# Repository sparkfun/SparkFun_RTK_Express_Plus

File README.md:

SparkFun RTK Express Plus
===========================================================

[*SparkFun RTK Express Plus (GPS-18590)*](https://www.sparkfun.com/products/18590)

he SparkFun RTK Express Plus is an easy to use GNSS receiver for centimeter-level positioning. Perfect for surveying, autonomous vehicles, logging, and all types of post processing, this preprogrammed device can also be used for autonomous driving, navigation, asset tracking and any other application where there is a clear view of the sky. The RTK Express Plus adds an internal IMU to combine real-time GNSS tracking with advanced sensor fusion. The result is accurate positioning even when GNSS is lost in tunnels, parking garages, etc. Out of the box an RTK Express Plus can be used with a correction source to create an RTK system capable of 14mm horizontal positional accuracy. The built-in Bluetooth® connection via an ESP32 WROOM enables the user to use the RTK Express Plus with their choice of GIS application on a phone or tablet. The built in battery allows for over five hours of field use and is compatible with common USB battery banks.

Repository Contents
-------------------

* **/Enclosure** - gcode for enclosure milling
* **/Graphics** - Bitmaps for the display
* **/Hardware** - Eagle files
* **/Overlay** - Design files for the adhesive membrane overlay

Documentation
--------------

* **[Hookup Guide](https://learn.sparkfun.com/tutorials/sparkfun-rtk-express-hookup-guide)** - Hookup guide for the SparkFun RTK Express.

License Information
-------------------

This product is _**open source**_!

Various bits of the code have different licenses applied. Anything SparkFun wrote is beerware; if you see me (or any other SparkFun employee) at the local, and you've found our code helpful, please buy us a round!

Please use, reuse, and modify these files as you see fit. Please maintain attribution to SparkFun Electronics and release anything derivative under the same license.

Distributed as-is; no warranty is given.

- Your friends at SparkFun.

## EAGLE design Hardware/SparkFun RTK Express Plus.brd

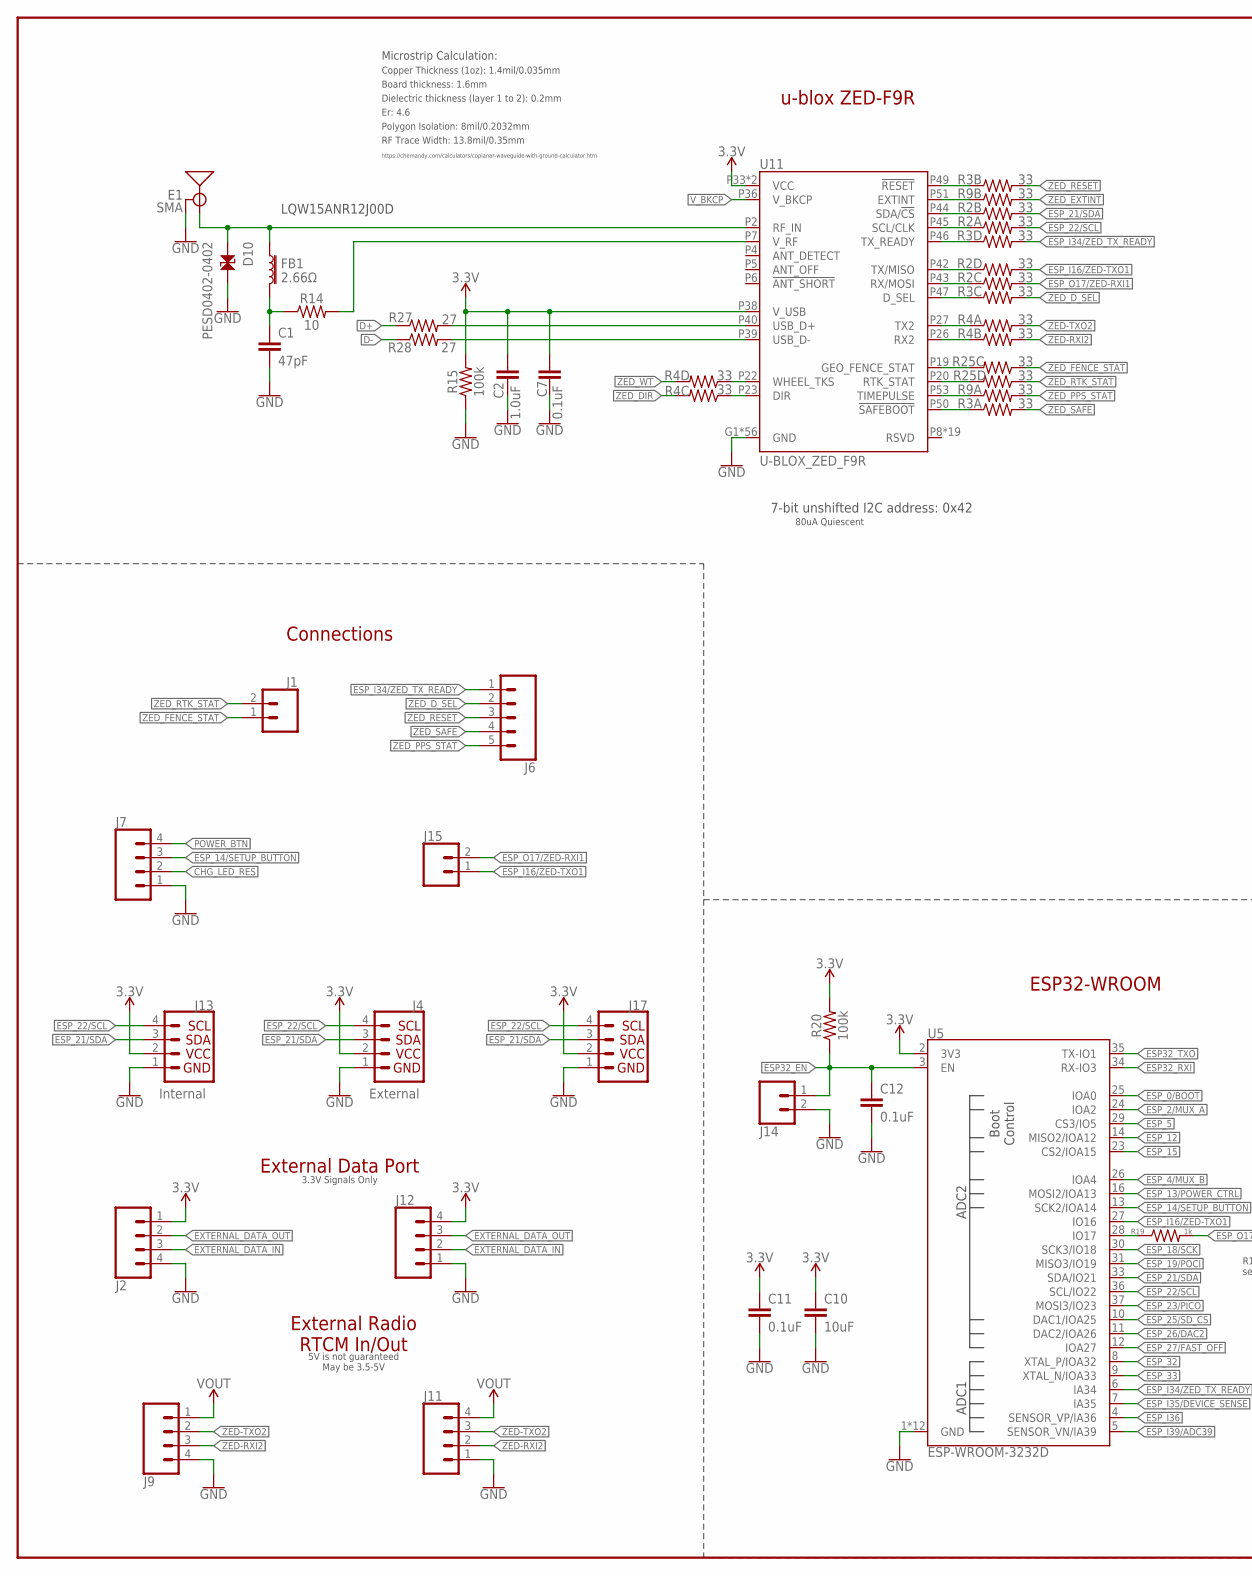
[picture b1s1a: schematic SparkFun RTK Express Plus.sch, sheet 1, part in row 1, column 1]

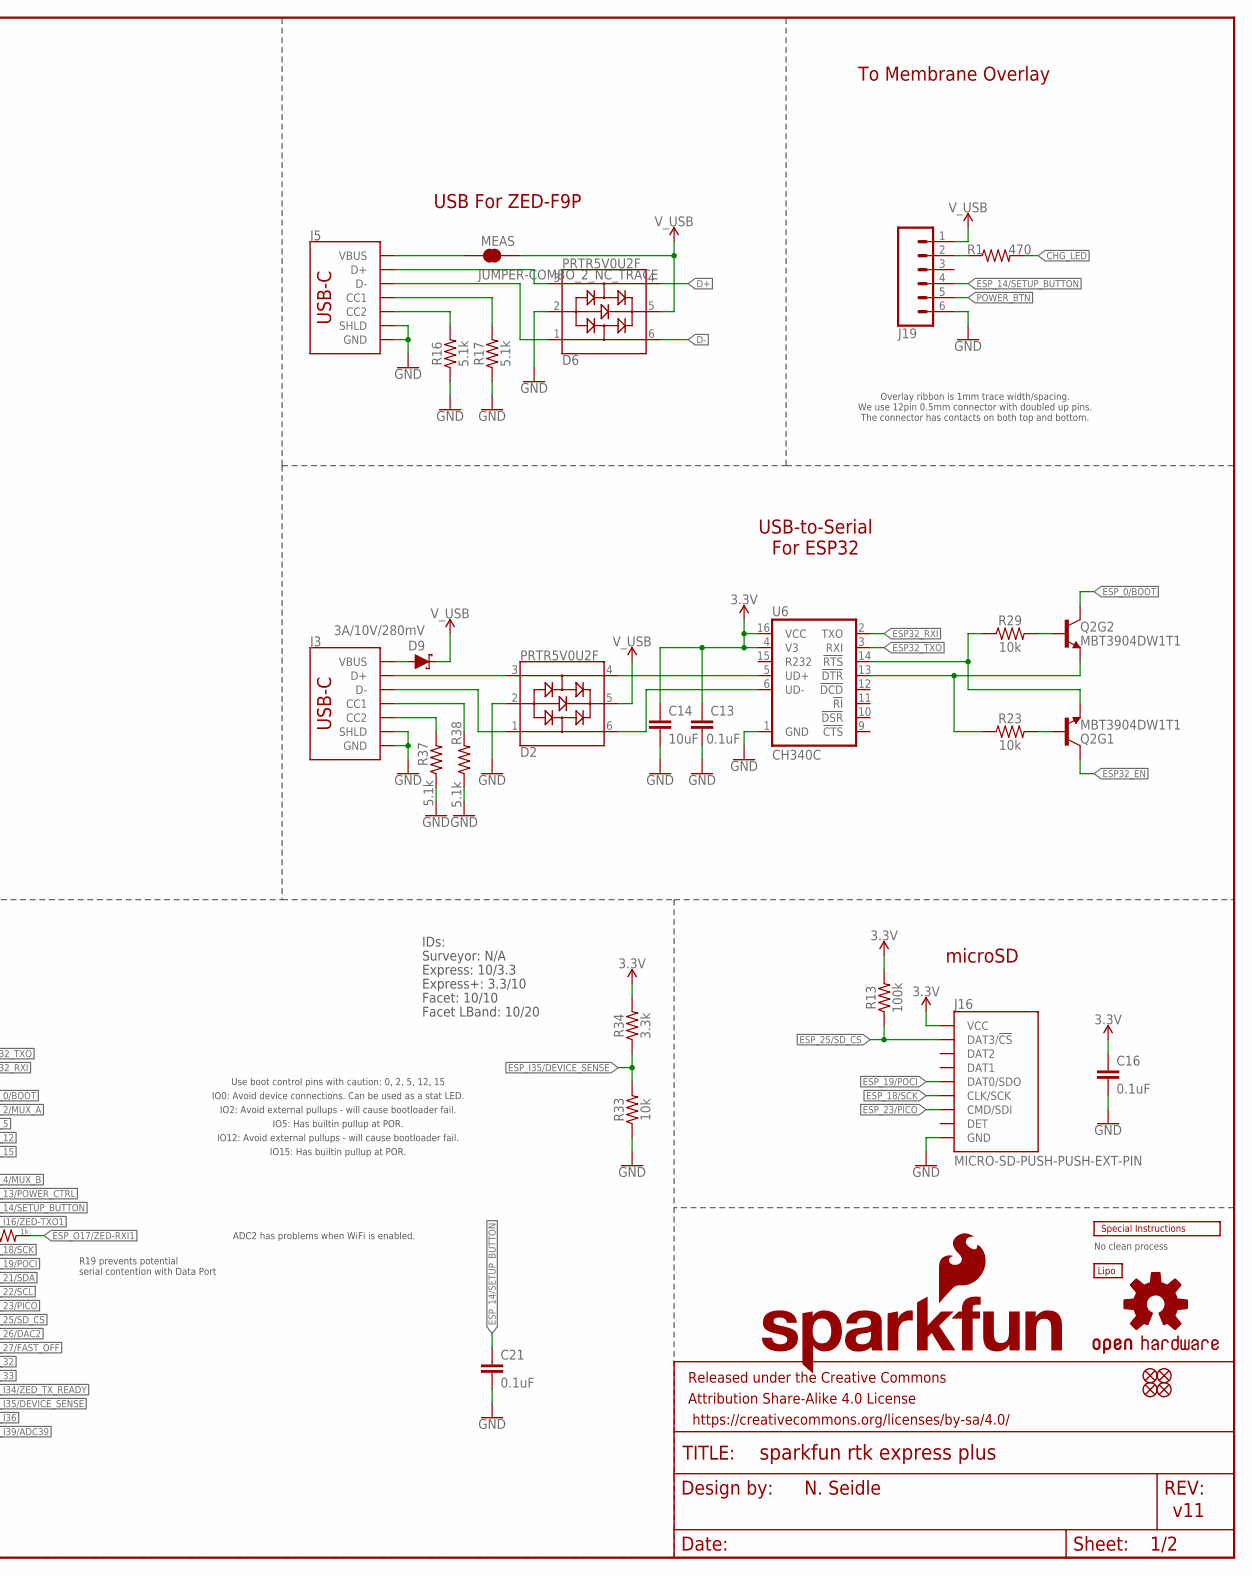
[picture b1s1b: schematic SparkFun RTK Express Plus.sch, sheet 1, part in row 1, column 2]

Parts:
BT1: LIPO-OUTLINE1000; LIPO-1000
C1: 47pF; 0402
C2: 1.0uF; 0603
C7, C11, C12, C13, C16, C21: 0.1uF; 0603
C10, C14: 10uF; 0603
D2, D6: PRTR5V0U2F; SOT886
D9: 3A/10V/280mV; SOD-323
D10: PESD0402-0402; 0402
E1: SMA; SMA-EDGE
FB1: 2.66Ω; 0402-TIGHT
FRAME2: FRAME-LEDGER; CREATIVE_COMMONS
J1, J14, J15: CONN_021X02_NO_SILK; 1X02_NO_SILK
J2, J9: CONN_04JST-SMD-LOCKING; JST-4-SMD-1.25MM-LOCKING
J3, J5: USB Female Type C Connector; USB-C-16P_4LAYER-PADS
J4: External; JST04_1MM_RA
J6: CONN_05NO_SILK; 1X05_NO_SILK
J7, J11, J12: CONN_041X04_NO_SILK_NO_POP; 1X04_NO_SILK
J13: Internal; JST04_1MM_RA
J16: MICRO-SD-PUSH-PUSH-EXT-PIN; MICROSD-EXTERNALPIN
J17: Qwiic Right Angle; 1X04_NO_SILK
J19: CONN_061MM-LIF; FPC_6_1MM-LIF
JP21, JP61, JP71, JP81: FIDUCIALUFIDUCIAL; FIDUCIAL-MICRO
LOGO1: OSHW-LOGOMINI; OSHW-LOGO-MINI
LOGO2: SFE_LOGO_NAME_FLAME.1_INCH; SFE_LOGO_NAME_FLAME_.1
MEAS: JUMPER-COMBO_2_NC_TRACE; COMBO-JUMPER_2_NC_TRACE
Q2: MBT3904DW1T1; SC70-6
R1: 470; 0603
R2, R3, R4, R9, R25: 33; 1206_RA
R13, R15, R20: 100k; 0603
R14: 10; 0603
R16, R17, R37, R38: 5.1k; 0603
R19: 1k; 0603
R23, R29, R33: 10k; 0603
R27, R28: 27; 0603
R34: 3.3k; 0603
U5: ESP-WROOM-3232D; ESP-WROOM-32D
U6: CH340C; SO016
U11: U-BLOX_ZED_F9R; UBLOX_ZED_F9R
U$2: SPECIAL_INSTRUCTIONS-ORDERING; ORDERING_INSTRUCTIONS

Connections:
3.3V: C2.1, C7.2, C10.1, C11.1, C13.1, C14.1, C16.1, J2.1, J4.2, J12.4, J13.2, J16.4 (VCC), J17.2, R13.2, R15.2, R20.2, R34.2, U5.2 (3V3), U6.4 (V3), U6.16 (VCC), U11.P33 (VCC), U11.P34 (VCC), U11.P38 (V_USB); also elsewhere on the board
ANT_VCC: C1.1, FB1.2, R14.1
CC1: J5.A5 (CC1), R17.2
CC2: J5.B5 (CC2), R16.2
CC3: J3.B5 (CC2), R37.2
CC4: J3.A5 (CC1), R38.2
CHG_LED: R1.2; also elsewhere on the board
CHG_LED_RES: J7.2, J19.2, R1.1
D+: D6.4, R27.1
D+1: D2.4, U6.5 (UD+)
D-: D6.6, R28.1
D-1: D2.6, U6.6 (UD-)
ESP32_!DTR: Q2.1 (E), R23.1, U6.13 (!DTR)
ESP32_!RTS: Q2.4 (E), R29.1, U6.14 (!RTS)
ESP32_EN: C12.1, J14.1, Q2.3 (C), R20.1, U5.3 (EN)
ESP32_RXI: U5.34 (RX-IO3), U6.2 (TXO)
ESP32_TXO: U5.35 (TX-IO1), U6.3 (RXI)
ESP_0/BOOT: Q2.6 (C), U5.25 (IOA0)
ESP_2/MUX_A: U5.24 (IOA2); also elsewhere on the board
ESP_4/MUX_B: U5.26 (IOA4); also elsewhere on the board
ESP_5: U5.29 (CS3/IO5)
ESP_12: U5.14 (MISO2/IOA12)
ESP_13/POWER_CTRL: U5.16 (MOSI2/IOA13); also elsewhere on the board
ESP_14/SETUP_BUTTON: C21.1, J7.3, J19.4, U5.13 (SCK2/IOA14)
ESP_15: U5.23 (CS2/IOA15)
ESP_18/SCK: J16.5 (CLK/SCK), U5.30 (SCK3/IO18)
ESP_19/POCI: J16.7 (DAT0/SDO), U5.31 (MISO3/IO19)
ESP_21/SDA: J4.3, J13.3, J17.3, R2.P7 (2), U5.33 (SDA/IO21); also elsewhere on the board
ESP_22/SCL: J4.4, J13.4, J17.4, R2.P8 (2), U5.36 (SCL/IO22); also elsewhere on the board
ESP_23/PICO: J16.3 (CMD/SDI), U5.37 (MOSI3/IO23)
ESP_25/SD_!CS!: J16.2 (DAT3/!CS!), R13.1, U5.10 (DAC1/IOA25)
ESP_26/DAC2: U5.11 (DAC2/IOA26); also elsewhere on the board
ESP_26/ZED_TX_READY_LV: R3.P4 (1), U11.P46 (TX_READY)
ESP_27/FAST_OFF: U5.12 (IOA27); also elsewhere on the board
ESP_32: U5.8 (XTAL_P/IOA32)
ESP_33: U5.9 (XTAL_N/IOA33)
ESP_D1+: D2.3, J3.A6 (D+), J3.B6 (D+)
ESP_D1-: D2.1, J3.A7 (D-), J3.B7 (D-)
ESP_I16/ZED-TXO1: J15.1, R2.P5 (2), U5.27 (IO16); also elsewhere on the board
ESP_I34/ZED_TX_READY: J6.1, R3.P5 (2), U5.6 (IA34)
ESP_I35/DEVICE_SENSE: R33.2, R34.1, U5.7 (IA35)
ESP_I36: U5.4 (SENSOR_VP/IA36)
ESP_I39/ADC39: U5.5 (SENSOR_VN/IA39); also elsewhere on the board
ESP_O17/ZED-RXI1: J15.2, R2.P6 (2), R19.2; also elsewhere on the board
EXTERNAL_DATA_IN: J2.3, J12.2; also elsewhere on the board
EXTERNAL_DATA_OUT: J2.2, J12.3; also elsewhere on the board
EXTINT_LV: R9.P2 (1), U11.P51 (EXTINT)
FENCE_LV: R25.P6 (2), U11.P19 (GEO_FENCE_STAT)
GND: C1.2, C2.2, C7.1, C10.2, C11.2, C12.2, C13.2, C14.2, C16.2, C21.2, D2.2, D6.2, D10.2, E1.GND@0 (GND), E1.GND@1 (GND), E1.GND@2 (GND), E1.GND@3 (GND), J2.4, J3.GND, J3.GND2 (GND), J3.SHLD1 (SHLD), J3.SHLD2 (SHLD), J3.SHLD3 (SHLD), J3.SHLD4 (SHLD), J4.1, J5.GND, J5.GND2 (GND), J5.SHLD1 (SHLD), J5.SHLD2 (SHLD), J5.SHLD3 (SHLD), J5.SHLD4 (SHLD), J7.1, J9.4, J11.1, J12.1, J13.1, J14.2, J16.6 (GND), J16.10 (GND), J16.11 (GND), J16.12 (GND), J16.13 (GND), J17.1, J19.6, R15.1, R16.1, R17.1, R33.1, R37.1, R38.1, U5.1 (GND), U5.15 (GND), U5.38 (GND), U5.GND, U5.GNDT1 (GND), U5.GNDT2 (GND), U5.GNDT3 (GND), U5.GNDT4 (GND), U5.GNDT5 (GND), U5.GNDT6 (GND), U5.GNDT7 (GND), U5.GNDT8 (GND), U6.1 (GND), U11.G1 (GND), U11.G2 (GND), U11.G3 (GND), U11.G4 (GND), U11.G5 (GND), U11.G6 (GND), U11.G7 (GND), U11.G8 (GND), U11.G9 (GND), U11.G10 (GND), U11.G11 (GND), U11.G12 (GND), U11.G13 (GND), U11.G14 (GND), U11.G15 (GND), U11.G16 (GND), U11.G17 (GND), U11.G18 (GND), U11.G19 (GND), U11.G20 (GND), U11.G21 (GND), U11.G22 (GND), U11.G23 (GND), U11.G24 (GND), U11.G25 (GND), U11.G26 (GND), U11.G27 (GND), U11.G28 (GND), U11.G29 (GND), U11.G30 (GND), U11.G31 (GND), U11.G32 (GND), U11.G33 (GND), U11.G34 (GND), U11.G35 (GND), U11.G36 (GND), U11.G37 (GND), U11.G38 (GND), U11.G39 (GND), U11.G40 (GND), U11.G41 (GND), U11.G42 (GND), U11.G43 (GND), U11.G44 (GND), U11.G45 (GND), U11.G46 (GND), U11.G47 (GND), U11.G48 (GND), U11.P1 (GND), U11.P3 (GND), U11.P12 (GND), U11.P14 (GND), U11.P32 (GND), U11.P37 (GND), U11.P41 (GND), U11.P48 (GND); also elsewhere on the board
GPS_ANT1: D10.1, E1.SIG (SIGNAL), FB1.1, U11.P2 (RF_IN)
unnamed: R4.P4 (1), U11.P22 (WHEEL_TKS)
unnamed: R4.P3 (1), U11.P23 (DIR)
unnamed: J5.VBUS1 (VBUS), J5.VBUS2 (VBUS), MEAS.1, MEAS.3 (1)
unnamed: R19.1, U5.28 (IO17)
unnamed: R27.2, U11.P40 (USB_D+)
unnamed: R28.2, U11.P39 (USB_D-)
unnamed: R14.2, U11.P7 (V_RF)
unnamed: Q2.5 (B), R23.2
unnamed: Q2.2 (B), R29.2
unnamed: D9.A, J3.VBUS1 (VBUS), J3.VBUS2 (VBUS)
POWER_BTN: J7.4, J19.5; also elsewhere on the board
PPS_LV: R9.P1 (1), U11.P53 (TIMEPULSE)
RTK_STAT_LV: R25.P5 (2), U11.P20 (RTK_STAT)
RX2_LV: R4.P2 (1), U11.P26 (RX2)
RXLV: R2.P3 (1), U11.P43 (RX/MOSI)
SCL_LV: R2.P1 (1), U11.P45 (SCL/CLK)
SDA_LV: R2.P2 (1), U11.P44 (SDA/!CS!)
TX2_LV: R4.P1 (1), U11.P27 (TX2)
TXLV: R2.P4 (1), U11.P42 (TX/MISO)
UNP_D+: D6.3, J5.A6 (D+), J5.B6 (D+)
UNP_D-: D6.1, J5.A7 (D-), J5.B7 (D-)
VOUT: J9.1, J11.4; also elsewhere on the board
V_BKCP: U11.P36 (V_BKCP); also elsewhere on the board
V_USB: D2.5, D6.5, D9.C, J19.1, MEAS.2, MEAS.4 (2); also elsewhere on the board
ZED-RXI2: J9.3, J11.2, R4.P7 (2)
ZED-TXO2: J9.2, J11.3, R4.P8 (2)
ZED_!RESET!: J6.3, R3.P7 (2)
ZED_!RESET!_LV: R3.P2 (1), U11.P49 (!RESET!)
ZED_!SAFE!: J6.4, R3.P8 (2)
ZED_!SAFE!_LV: R3.P1 (1), U11.P50 (!SAFEBOOT!)
ZED_DIR: R4.P6 (2); also elsewhere on the board
ZED_D_SEL: J6.2, R3.P6 (2)
ZED_D_SEL_LV: R3.P3 (1), U11.P47 (D_SEL)
ZED_EXTINT: R9.P7 (2); also elsewhere on the board
ZED_FENCE_STAT: J1.1, R25.P3 (1)
ZED_PPS_STAT: J6.5, R9.P8 (2); also elsewhere on the board
ZED_RTK_STAT: J1.2, R25.P4 (1)
ZED_WT: R4.P5 (2); also elsewhere on the board

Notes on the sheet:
v11
7-bit unshifted I2C address: 0x42
u-blox ZED-F9R
LQW15ANR12J00D
Board thickness: 1.6mm
Er: 4.6
Copper Thickness (1oz): 1.4mil/0.035mm
RF Trace Width: 13.8mil/0.35mm
Polygon Isolation: 8mil/0.2032mm
No clean process
Dielectric thickness (layer 1 to 2): 0.2mm
https://chemandy.com/calculators/coplanar-waveguide-with-ground-calculator.htm
Microstrip Calculation:
Connections
External Radio RTCM In/Out
External Data Port
ESP32-WROOM
USB-to-Serial For ESP32
microSD
5V is not guaranteed May be 3.5-5V
USB For ZED-F9P
N. Seidle
R19 prevents potential serial contention with Data Port
80uA Quiescent
To Membrane Overlay
Overlay ribbon is 1mm trace width/spacing. We use 12pin 0.5mm connector with doubled up pins. The connector has contacts on both top and bottom.
IO0: Avoid device connections. Can be used as a stat LED.
ADC2 has problems when WiFi is enabled.
IO12: Avoid external pullups - will cause bootloader fail.
Use boot control pins with caution: 0, 2, 5, 12, 15
IO2: Avoid external pullups - will cause bootloader fail.
IO15: Has builtin pullup at POR.
IO5: Has builtin pullup at POR.
3.3V Signals Only
IDs:
Surveyor: N/A
Express: 10/3.3
Express+: 3.3/10
Facet: 10/10
Facet LBand: 10/20

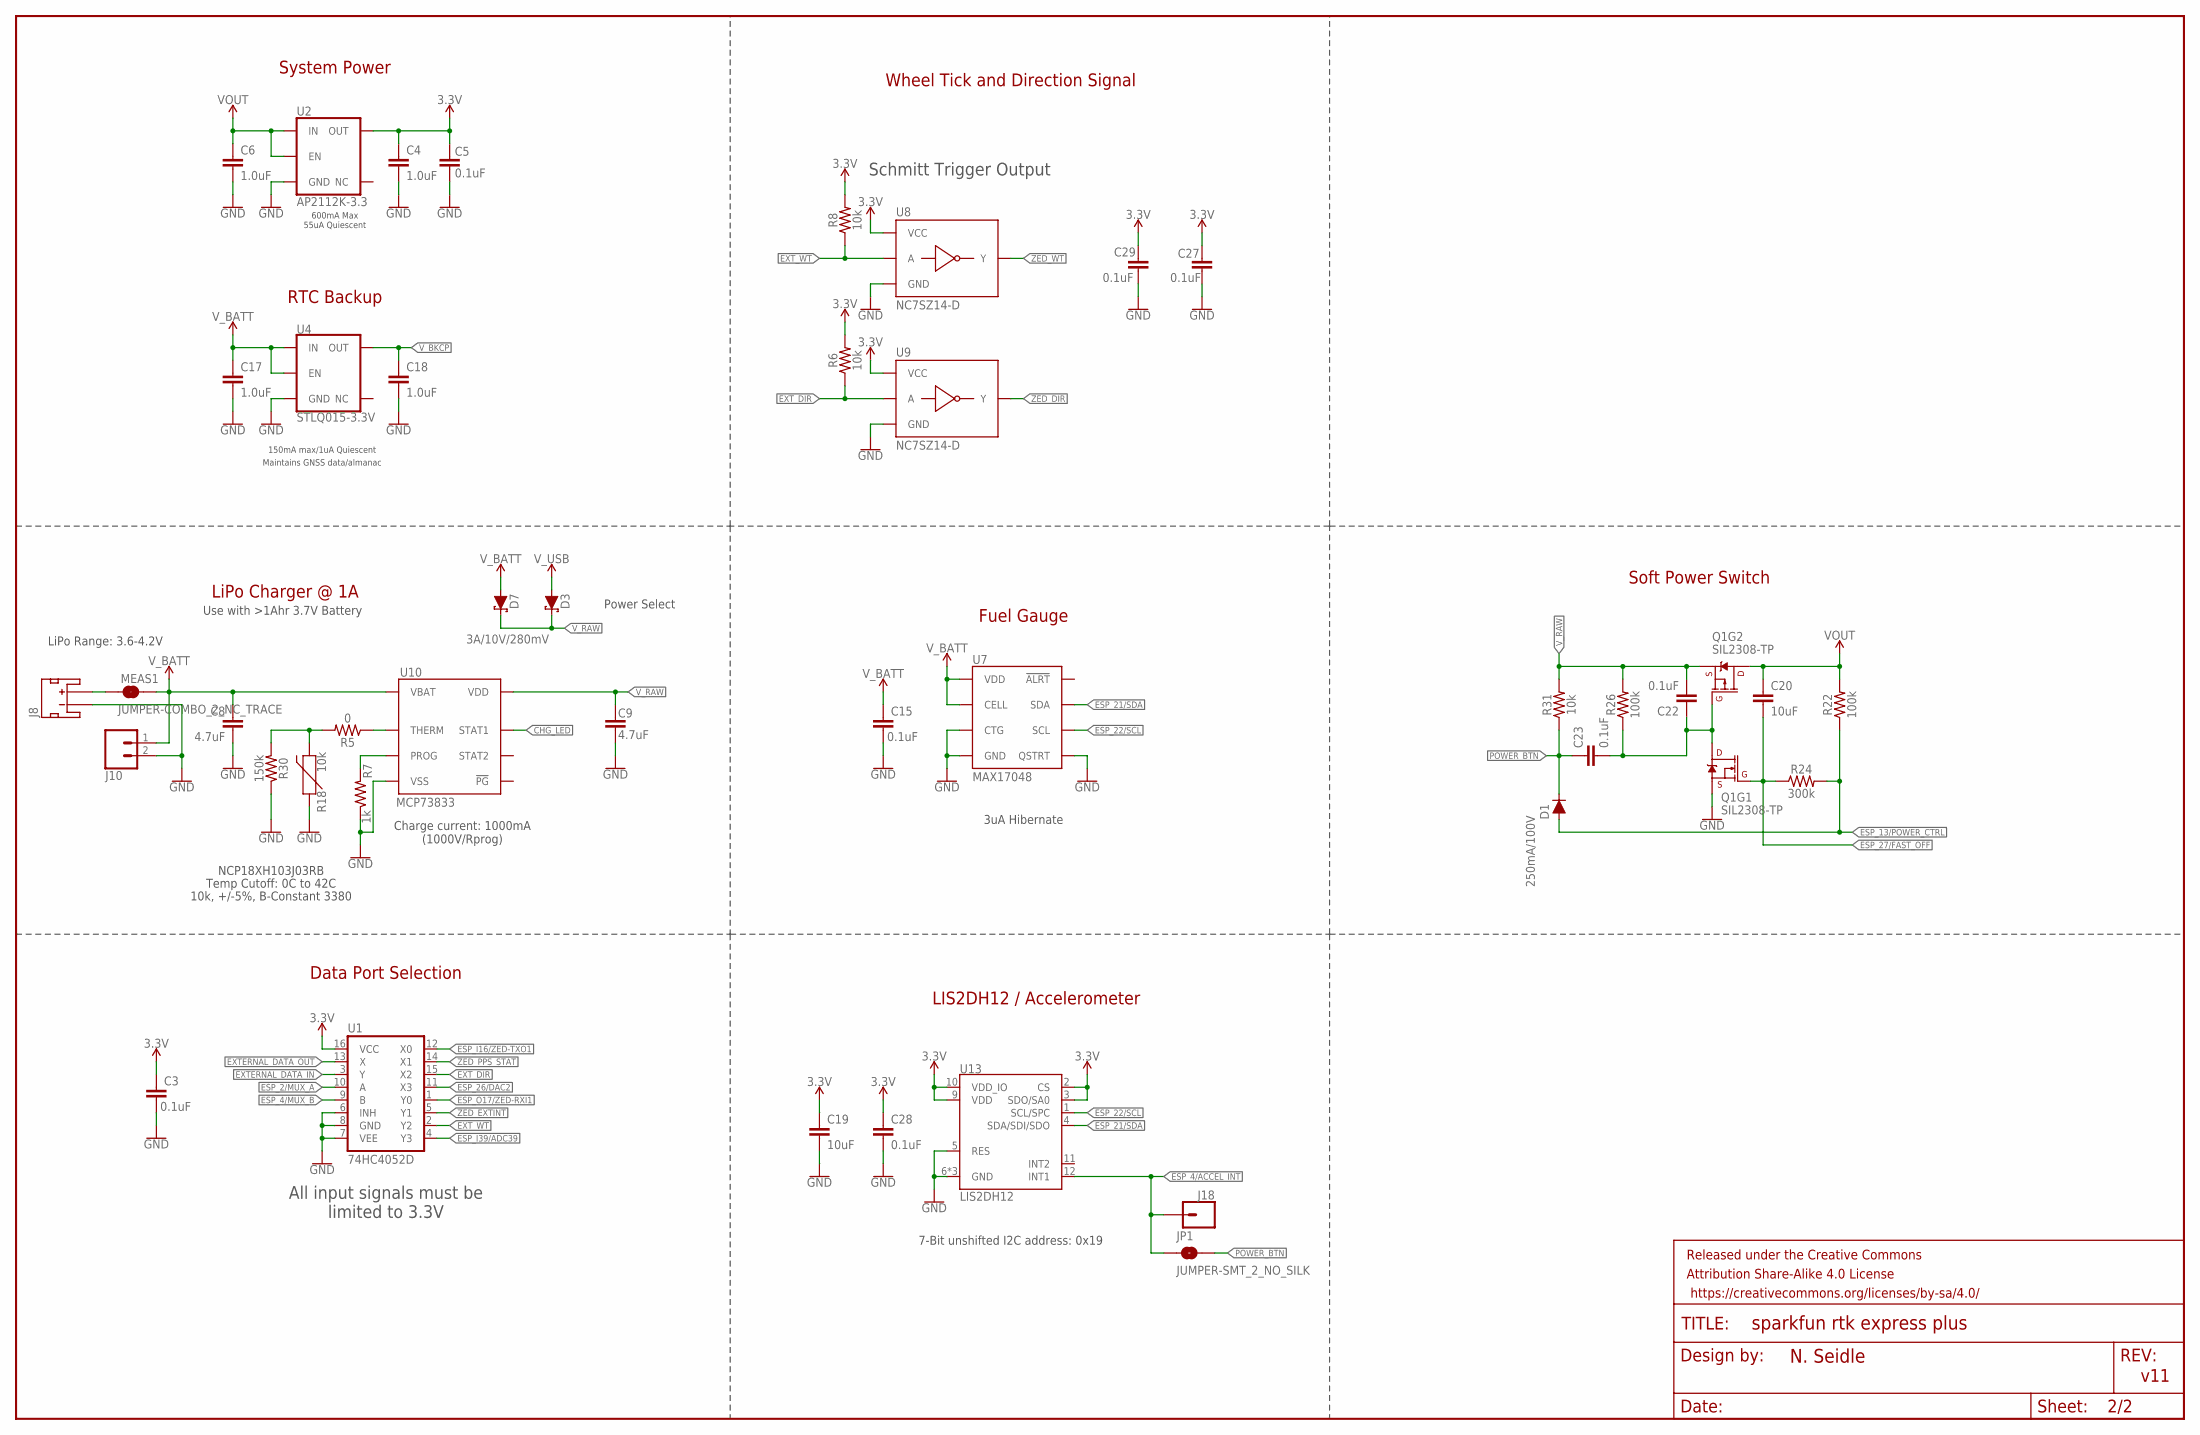
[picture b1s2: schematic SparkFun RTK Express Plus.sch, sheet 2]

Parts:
C3, C5, C15, C22, C23, C27, C28, C29: 0.1uF; 0603
C4, C6, C17, C18: 1.0uF; 0603
C8, C9: 4.7uF; 0603
C19, C20: 10uF; 0603
D1: 250mA/100V; SOD-323
D3, D7: 3A/10V/280mV; SOD-323
FRAME3: FRAME-LEDGERNO_FOOTPRINT; DUMMY
J8: JST_2MM_MALE; JST-2-SMD
J10: CONN_021X02_NO_SILK; 1X02_NO_SILK
J18: CONN_01PTH_NO_SILK_YES_STOP; 1X01_NO_SILK
JP1: JUMPER-SMT_2_NO_SILK; SMT-JUMPER_2_NO_SILK
MEAS1: JUMPER-COMBO_2_NC_TRACE; COMBO-JUMPER_2_NC_TRACE
Q1: SIL2308-TP; SOT26
R5: 0; 0603
R6, R8, R18, R31: 10k; 0603
R7: 1k; 0603
R22, R26: 100k; 0603
R24: 300k; 0603
R30: 150k; 0603
U1: 74HC4052D; SO16
U2: AP2112K-3.3; SOT23-5
U4: STLQ015-3.3V; SOT23-5
U7: MAX17048; DFN-8
U8, U9: NC7SZ14-D; SIP6
U10: MCP73833; DFN-10
U13: LIS2DH12; LGA-12-LISDH12

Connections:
3.3V: C3.1, C4.1, C5.2, C19.1, C27.1, C28.1, C29.1, R6.2, R8.2, U1.16 (VCC), U2.5 (OUT), U8.P6 (VCC), U9.P6 (VCC), U13.2 (CS), U13.3 (SDO/SA0), U13.9 (VDD), U13.10 (VDD_IO); also elsewhere on the board
CHG_LED: U10.3 (STAT1); also elsewhere on the board
CHG_THERM1: R5.2, R18.2, R30.2
ESP_2/MUX_A: U1.10 (A); also elsewhere on the board
ESP_4/ACCEL_INT: J18.1, JP1.1, U13.12 (INT1)
ESP_4/MUX_B: U1.9 (B); also elsewhere on the board
ESP_13/POWER_CTRL: D1.A, R22.1, R24.2; also elsewhere on the board
ESP_21/SDA: U7.8 (SDA), U13.4 (SDA/SDI/SDO); also elsewhere on the board
ESP_22/SCL: U7.7 (SCL), U13.1 (SCL/SPC); also elsewhere on the board
ESP_26/DAC2: U1.11 (X3); also elsewhere on the board
ESP_27/FAST_OFF: C20.2, Q1.G1 (G), R24.1; also elsewhere on the board
ESP_I16/ZED-TXO1: U1.12 (X0); also elsewhere on the board
ESP_I39/ADC39: U1.4 (Y3); also elsewhere on the board
ESP_O17/ZED-RXI1: U1.1 (Y0); also elsewhere on the board
EXTERNAL_DATA_IN: U1.3 (Y); also elsewhere on the board
EXTERNAL_DATA_OUT: U1.13 (X); also elsewhere on the board
EXT_DIR: R6.1, U1.15 (X2), U9.P2 (A)
EXT_WT: R8.1, U1.2 (Y2), U8.P2 (A)
GND: C3.2, C4.2, C5.1, C6.2, C8.2, C9.2, C15.2, C17.2, C18.2, C19.2, C27.2, C28.2, C29.2, J8.1 (-), J10.2, Q1.S1 (S), R7.1, R18.1, R30.1, U1.6 (INH), U1.7 (VEE), U1.8 (GND), U2.2 (GND), U4.2 (GND), U7.1 (CTG), U7.4 (GND), U7.6 (QSTRT), U7.9 (GND), U8.P3 (GND), U9.P3 (GND), U10.5 (VSS), U10.11 (VSS), U13.5 (RES), U13.6 (GND), U13.7 (GND), U13.8 (GND); also elsewhere on the board
LIPO_RAW: J8.2 (+), MEAS1.1, MEAS1.3 (1)
unnamed: R5.1, U10.8 (THERM)
unnamed: C22.1, C23.2, Q1.D1 (D), Q1.G2 (G), R26.1
POWER_BTN: C23.1, D1.C, JP1.2, R31.1; also elsewhere on the board
PROG1: R7.2, U10.6 (PROG)
VOUT: C6.1, C20.1, Q1.D2 (D), R22.2, U2.1 (IN), U2.3 (EN); also elsewhere on the board
V_BATT: C8.1, C15.1, C17.1, D7.A, J10.1, MEAS1.2, MEAS1.4 (2), U4.1 (IN), U4.3 (EN), U7.2 (CELL), U7.3 (VDD), U10.9 (VBAT), U10.10 (VBAT)
V_BKCP: C18.1, U4.5 (OUT); also elsewhere on the board
V_RAW: C9.1, C22.2, D3.C, D7.C, Q1.S2 (S), R26.2, R31.2, U10.1 (VDD), U10.2 (VDD)
V_USB: D3.A; also elsewhere on the board
ZED_DIR: U9.P4 (Y); also elsewhere on the board
ZED_EXTINT: U1.5 (Y1); also elsewhere on the board
ZED_PPS_STAT: U1.14 (X1); also elsewhere on the board
ZED_WT: U8.P4 (Y); also elsewhere on the board

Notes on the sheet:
LiPo Range: 3.6-4.2V
Charge current: 1000mA (1000V/Rprog)
Use with >1Ahr 3.7V Battery
LiPo Charger @ 1A
NCP18XH103J03RB
10k, +/-5%, B-Constant 3380
Temp Cutoff: 0C to 42C
Fuel Gauge
Data Port Selection
Power Select
3uA Hibernate
7-Bit unshifted I2C address: 0x19
LIS2DH12 / Accelerometer
Soft Power Switch
RTC Backup
System Power
600mA Max 55uA Quiescent
150mA max/1uA Quiescent
Maintains GNSS data/almanac
Wheel Tick and Direction Signal
Schmitt Trigger Output
All input signals must be limited to 3.3V
v11

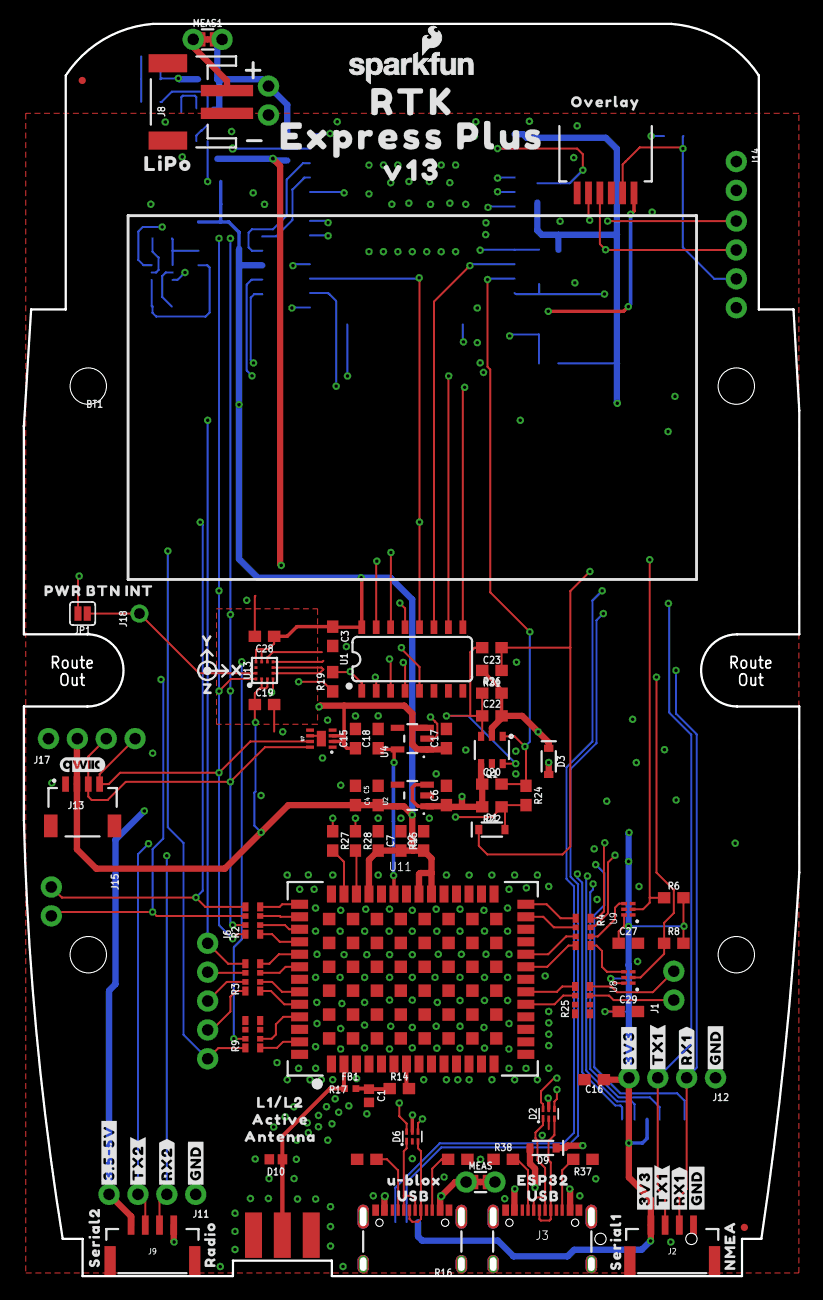
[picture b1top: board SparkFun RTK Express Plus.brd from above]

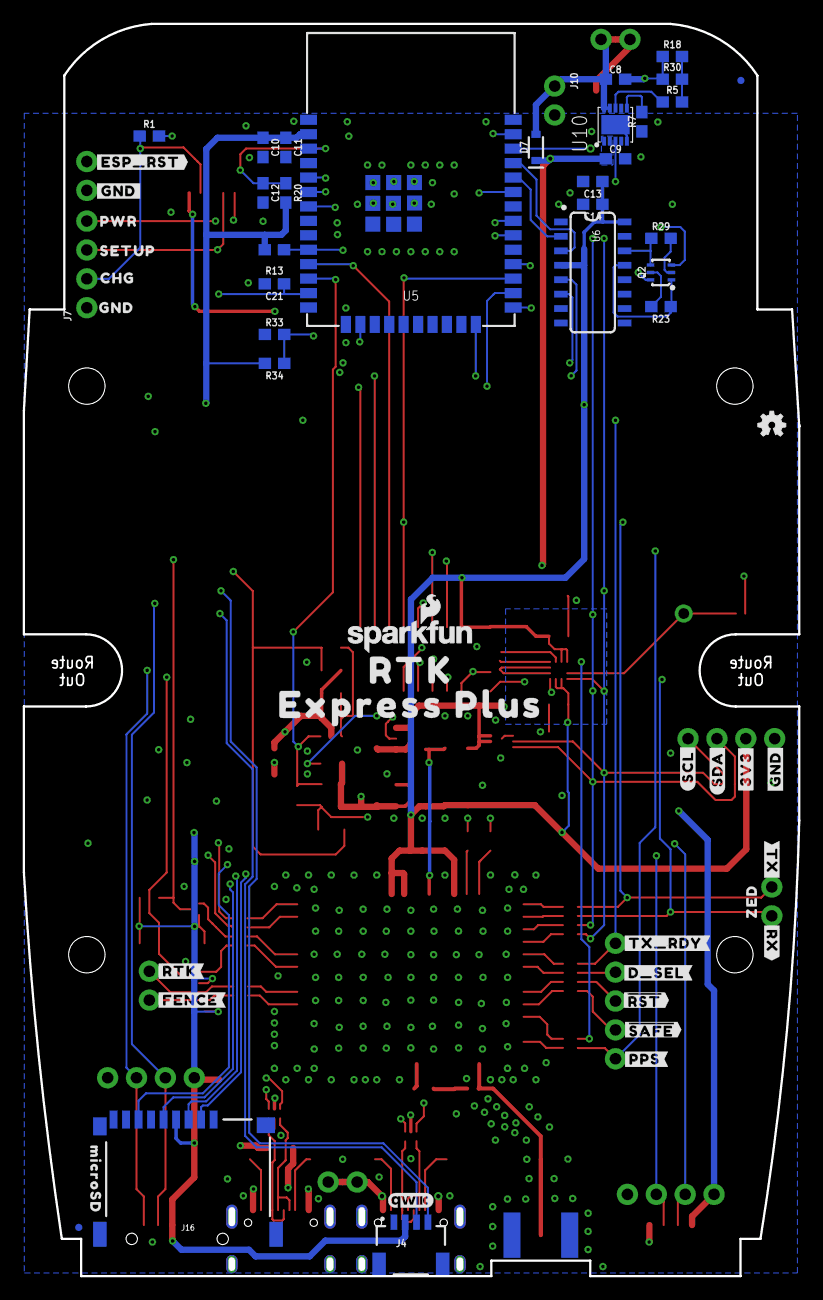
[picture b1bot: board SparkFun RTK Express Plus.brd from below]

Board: 4 copper layers, 68.2 x 110.1 mm, 171 parts (56 on the bottom side), 92 nets.

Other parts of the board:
LOGO3: SFE_LOGO_NAME_FLAME.1_INCH; SFE_LOGO_NAME_FLAME_.1
U$1: V130
U$3: #TX_RDY#0
U$4: INT0
U$5, U$47: #3V3#0
U$6: L1#L20
U$7, U$74: RTK0
U$8: OVERLAY0
U$9: PWR_BTN1
U$10: #RTK#1
U$11: #PPS#0
U$12, U$22: EXPRESS_PLUS0
U$13: ACTIVE1
U$14: #RX#2
U$15: ANTENNA2
U$16: ZED0
U$17: ##SAFE##5
U$23: #3#5#5V#0
U$24: X0
U$26: 1553DBK-ENCLOSURE
U$27: LIPO0
U$28: ##RST##4
U$29: SERIAL10
U$30, U$93: QWIIC_4MM
U$32: #FENCE#3
U$33: CHG2
U$34: GND3
U$35: U#BLOX0
U$36, U$66: USB1
U$38, U$48, U$82: #GND#0
U$39: #RX2#2
U$40: #TX2#1
U$41: PWR0
U$42: SETUP1
U$43: SERIAL20
U$45, U$68: #RX1#2
U$46, U$65: #TX1#1
U$49: NMEA1
U$50: RADIO0
U$55: Y1
U$56: Z2
U$60: #ESP_RST#0
U$67: ESP320
U$70: #GND#2
U$72: #TX#1
U$83: MICROSD0
U$84: #GND#1
U$85: #3V3#2
U$86: #SCL#1
U$87: #SDA#0
U$88: #D_SEL#0

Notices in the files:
parts and their libraries:
SparkFun-Resistors: Licensing: Creative Commons ShareAlike 4.0 International - https://creativecommons.org/licenses/by-sa/4.0
SparkFun-Aesthetics: Released under the Creative Commons Attribution Share-Alike 4.0 License
SparkFun-Aesthetics: https://creativecommons.org/licenses/by-sa/4.0
